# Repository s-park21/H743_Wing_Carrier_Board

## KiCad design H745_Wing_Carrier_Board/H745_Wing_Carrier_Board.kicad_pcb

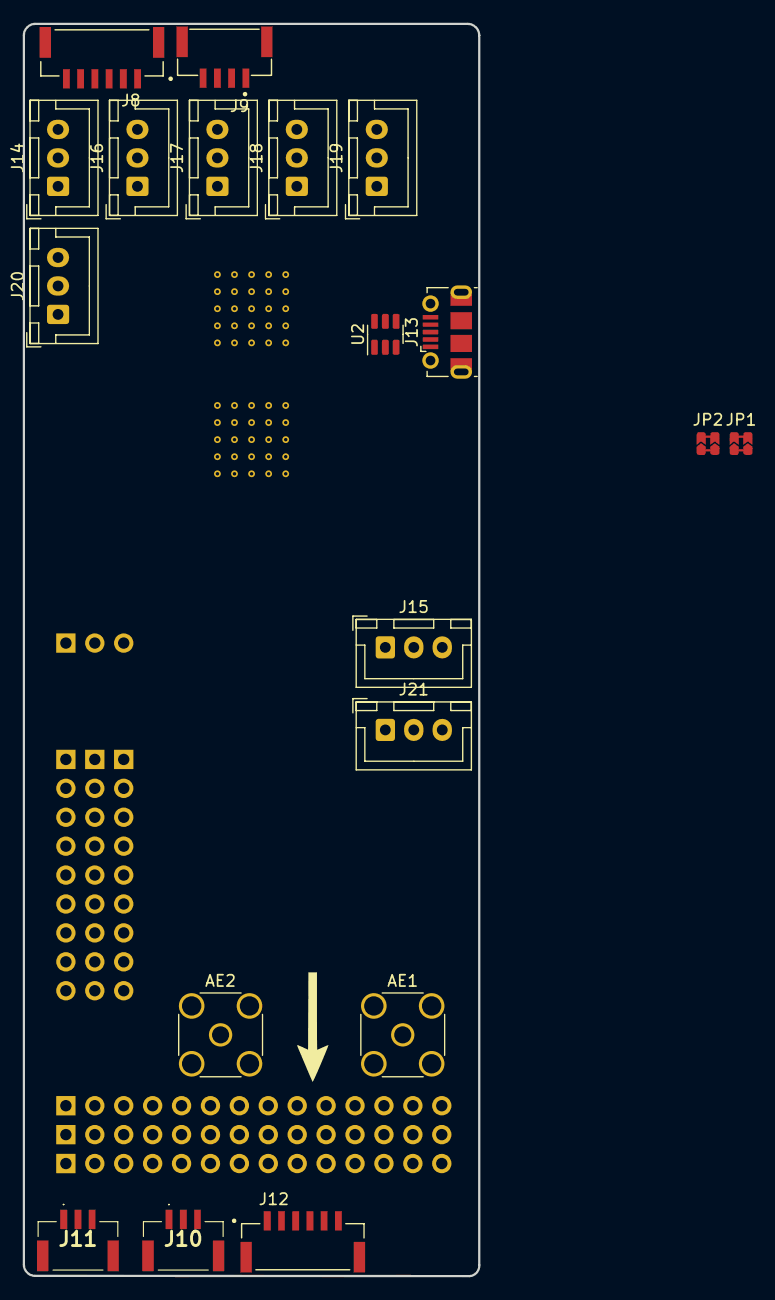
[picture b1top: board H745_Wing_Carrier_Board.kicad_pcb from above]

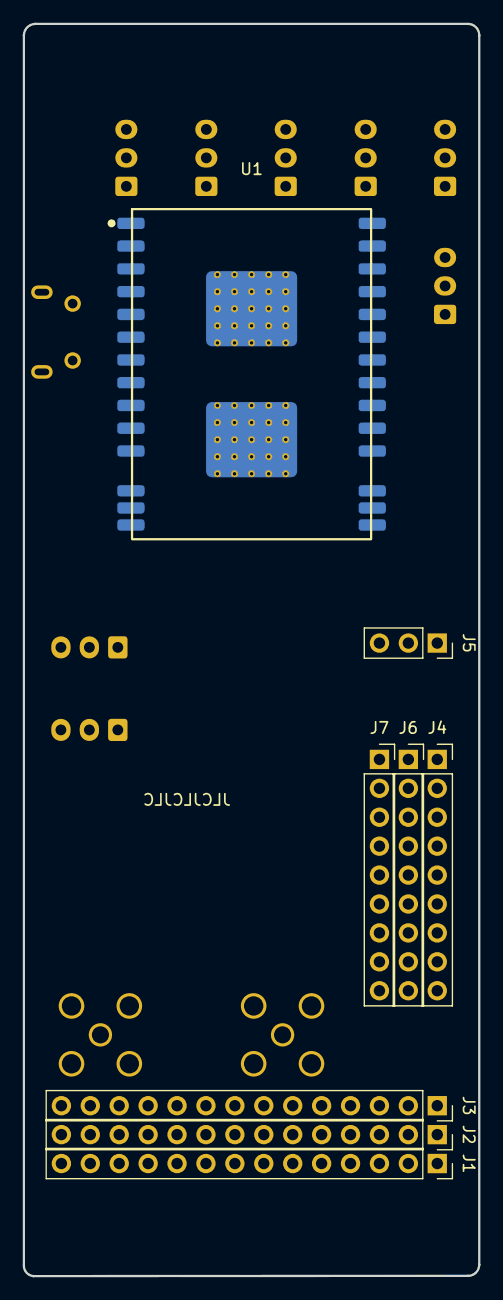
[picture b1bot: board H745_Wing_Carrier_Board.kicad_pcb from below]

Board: 4 copper layers, 40.0 x 110.0 mm, 27 parts (8 on the bottom side), 34 nets, no tracks yet.

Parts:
AE1, AE2: Antenna_Shield; SMA_Amphenol_132134-16_Vertical
J1, J2, J3: Conn_01x14; PinSocket_1x14_P2.54mm_Vertical
J4, J6, J7: Conn_01x09; PinSocket_1x09_P2.54mm_Vertical
J5: Conn_01x03; PinSocket_1x03_P2.54mm_Vertical
J8, J12: SM06B-GHS-TB(LF)(SN); JST_SM06B-GHS-TB(LF)(SN)
J9: SM04B-GHS-TB(LF)(SN)-; JST_SM04B-GHS-TB(LF)(SN)-
J10, J11: SM03B-GHS-TB(LF)(SN)-; JST_SM03B-GHS-TB(LF)(SN)-
J13: USB_B_Micro; USB_Micro-B_Molex-105017-0001
J14, J15, J16, J17, J18, J19, J20, J21: JST 3 Pin; JST_XH_B3B-XH-A_1x03_P2.50mm_Vertical
JP1, JP2: UART_Switch
U1: RFD900ux
U2: USBLC6-2SC6; SOT-23-6

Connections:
+5V: J1.2, J3.13, J8.1, J15.1, J21.1, U1.1 (VUSB), U1.19 (+5VIN)
+9V: J1.5, J2.5, J10.1, J12.6
/Camera1: J2.4, J10.3
/Camera2: J3.4, J11.3
/Connector_Breakouts/Servo1_PWM: J5.3, J14.2
/Connector_Breakouts/Servo2_PWM: J7.1, J16.2
/Connector_Breakouts/Servo3_PWM: J7.2, J17.2
/Connector_Breakouts/Servo4_PWM: J7.3, J18.2
/Connector_Breakouts/Servo5_PWM: J7.4, J19.2
/Connector_Breakouts/Servo6_PWM: J7.5, J20.2
/Connector_Breakouts/Servo_PWR: J5.2, J6.1, J6.2, J6.3, J6.4, J6.5, J6.6, J6.7, J6.8, J6.9, J14.1, J16.1, J17.1, J18.1, J19.1, J20.1
/Cts7: J3.9, J8.5
/LED: J1.3, J15.2, J21.2
/Peripheral_Breakouts/4v5: J1.13, J2.13
/Peripheral_Breakouts/Vx: J2.2, J3.2
/RFD900ux/ANT1: AE2.1 (A), U1.16 (ANT2)
/RFD900ux/ANT2: AE1.1 (A), U1.13 (ANT1)
/RFD900ux/SiCTS: JP1.3 (TX1), U1.28 (SiCTS)
/RFD900ux/SiRTS: JP1.1 (RX1), U1.27 (SiRTS)
/RFD900ux/SiRX: JP2.3 (TX1), U1.25 (SiRX)
/RFD900ux/SiTX: JP2.1 (RX1), U1.26 (SiTX)
/RFD900ux/USB2_D+: J13.3 (D+), U2.1 (I/O1)
/RFD900ux/USB2_D-: J13.2 (D-), U2.3 (I/O2)
/RFD900ux/USB_D+: U1.3 (USB_DP), U2.6 (I/O1)
/RFD900ux/USB_D-: U1.2 (USB_DM), U2.4 (I/O2)
/Rts7: J3.10, J8.4
/Rx1: J3.8, JP2.4 (RX2)
/Rx7: J3.12, J8.3
/Tx1: J3.7, JP2.2 (TX1)
/Tx7: J3.11, J8.2
/VTX_Out: J1.4, J12.4
/Vsw: J3.5, J11.1
GND: AE1.2 (Shield), AE2.2 (Shield), J1.1, J1.6, J1.14, J2.1, J2.6, J2.14, J3.1, J3.6, J3.14, J4.1, J4.2, J4.3, J4.4, J4.5, J4.6, J4.7, J4.8, J4.9, J5.1, J8.6, J8.S1 (SHIELD), J8.S2 (SHIELD), J9.1, J10.2, J11.2, J12.1, J12.2, J12.5, J12.S1 (SHIELD), J12.S2 (SHIELD), J13.5 (GND), J13.6 (Shield), J14.3, J15.3, J16.3, J17.3, J18.3, J19.3, J20.3, J21.3, U1.8 (GND), U1.9 (GND), U1.11 (GND), U1.12 (GND), U1.14 (GND), U1.15 (GND), U1.17 (GND), U1.18 (GND), U1.20 (GND), U2.2 (GND)
VBUS: J13.1 (VBUS), U2.5 (VBUS)

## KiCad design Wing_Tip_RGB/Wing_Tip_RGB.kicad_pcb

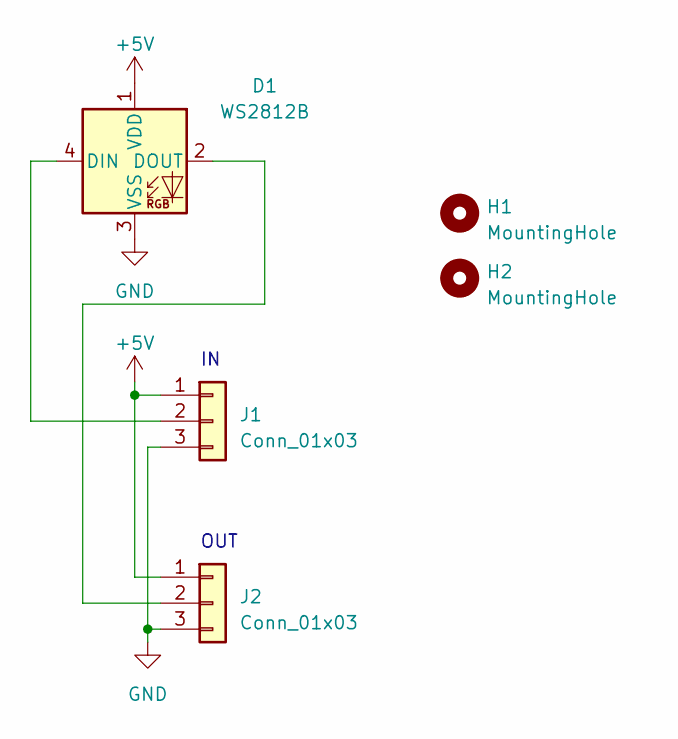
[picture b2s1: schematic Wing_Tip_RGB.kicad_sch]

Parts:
D1: WS2812B; LED_WS2812B_PLCC4_5.0x5.0mm_P3.2mm
H1, H2: MountingHole; MountingHole_2.2mm_M2_DIN965_Pad
J1, J2: Conn_01x03; JST_PH_B3B-PH-K_1x03_P2.00mm_Vertical

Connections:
+5V: D1.1 (VDD), J1.1, J2.1
GND: D1.3 (VSS), J1.3, J2.3
unnamed: D1.4 (DIN), J1.2
unnamed: D1.2 (DOUT), J2.2

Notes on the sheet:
OUT

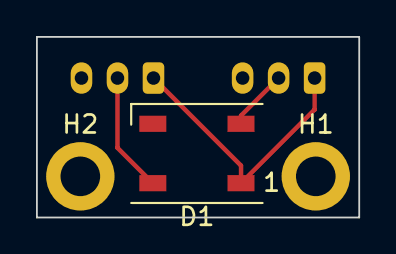
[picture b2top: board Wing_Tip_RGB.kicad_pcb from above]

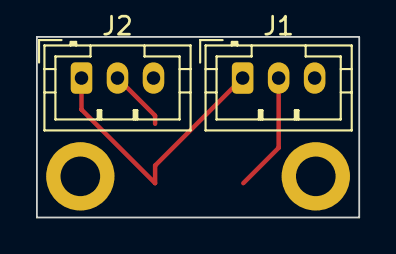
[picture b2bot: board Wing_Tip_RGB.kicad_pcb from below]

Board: 2 copper layers, 17.9 x 10.0 mm, 5 parts (2 on the bottom side), 4 nets.

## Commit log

2022-07-13 Inital commit
2022-11-20 Added RFD900ux library
2022-11-23 Added rfd900ux
2023-08-19 Added footprints for ux
2023-11-08 Fixed layout
2024-09-29 Traced together some stuff:
